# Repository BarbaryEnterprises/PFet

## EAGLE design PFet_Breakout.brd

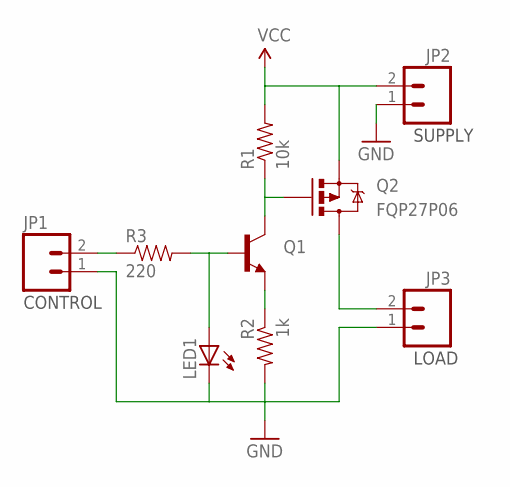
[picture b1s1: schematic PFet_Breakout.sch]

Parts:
JP1: M02PTH; 1X02
JP2, JP3: M023.5MM; SCREWTERMINAL-3.5MM-2
LED1: LED5MM
Q1: TRANSISTOR_NPNP2N2222A; TO-92
Q2: MOSFET-PCHANNELFQP27P06; TO220V
R1: 10k; AXIAL-0.3
R2: 1k; AXIAL-0.3
R3: 220; AXIAL-0.3

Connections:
GND: JP1.1, JP2.1, JP3.1, LED1.K (C), R2.P$2 (2)
unnamed: Q1.3 (E), R2.P$1 (1)
unnamed: LED1.A, Q1.2 (B), R3.P$2 (2)
unnamed: JP1.2, R3.P$1 (1)
unnamed: JP3.2, Q2.2 (D)
unnamed: Q1.1 (C), Q2.1 (G), R1.P$1 (1)
VCC: JP2.2, Q2.3 (S), R1.P$2 (2)

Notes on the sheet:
LOAD
CONTROL
SUPPLY
FQP27P06

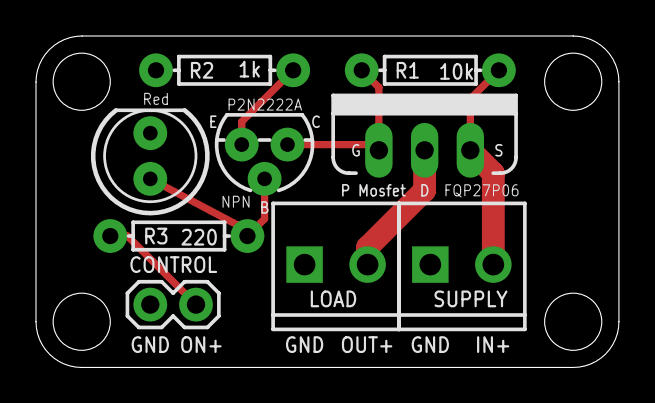
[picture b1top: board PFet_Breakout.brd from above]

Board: 2 copper layers, 32.4 x 18.4 mm, 9 parts (0 on the bottom side), 7 nets.

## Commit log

2014-05-05 added pdf and moved supply to right side of schematic;

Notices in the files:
parts and their libraries:
SparkFun-DiscreteSemi: Licensing: Creative Commons ShareAlike 4.0 International - https://creativecommons.org/licenses/by-sa/4.0
